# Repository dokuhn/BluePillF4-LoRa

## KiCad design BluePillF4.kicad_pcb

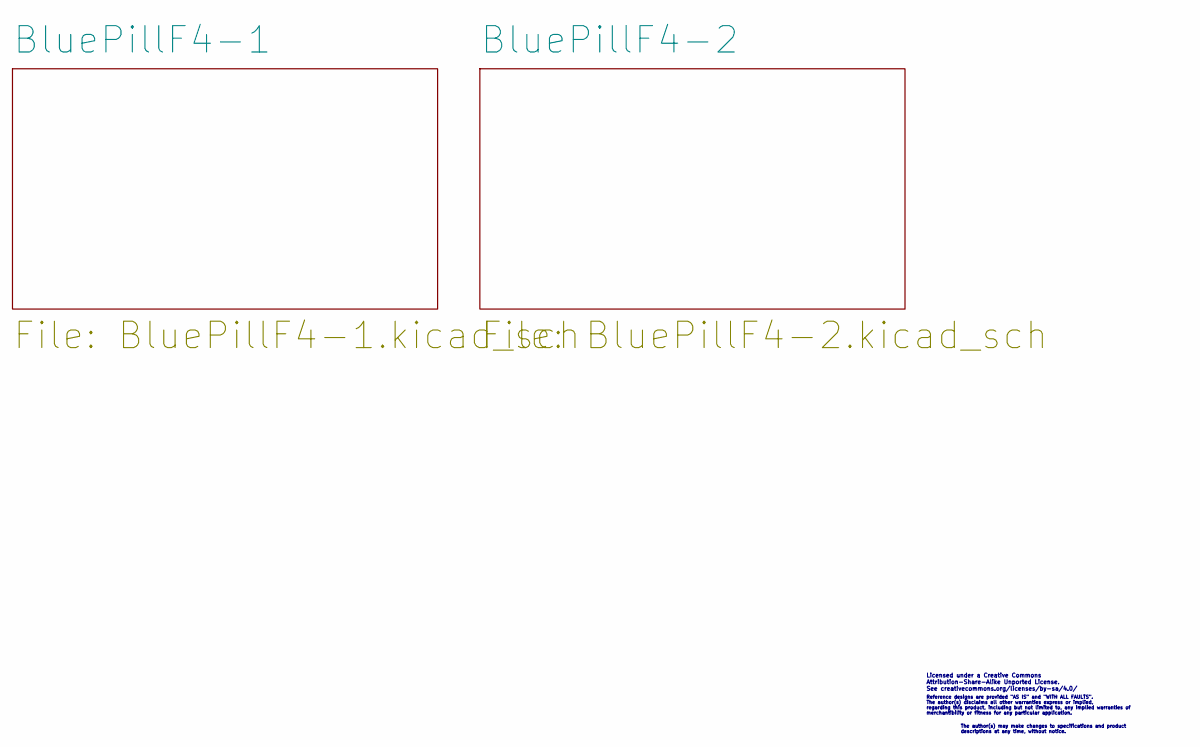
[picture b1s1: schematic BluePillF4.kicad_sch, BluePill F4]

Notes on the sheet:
Licensed under a Creative Commons Attribution-Share-Alike Unported License. See creativecommons.org/licenses/by-sa/4.0/
regarding this product, including but not limited to, any implied warranties of
merchantibility or fitness for any particular application.
Reference designs are provided "AS IS" and "WITH ALL FAULTS".
The author(s) disclaims all other warranties express or implied,
descriptions at any time, without notice.
The author(s) may make changes to specifications and product

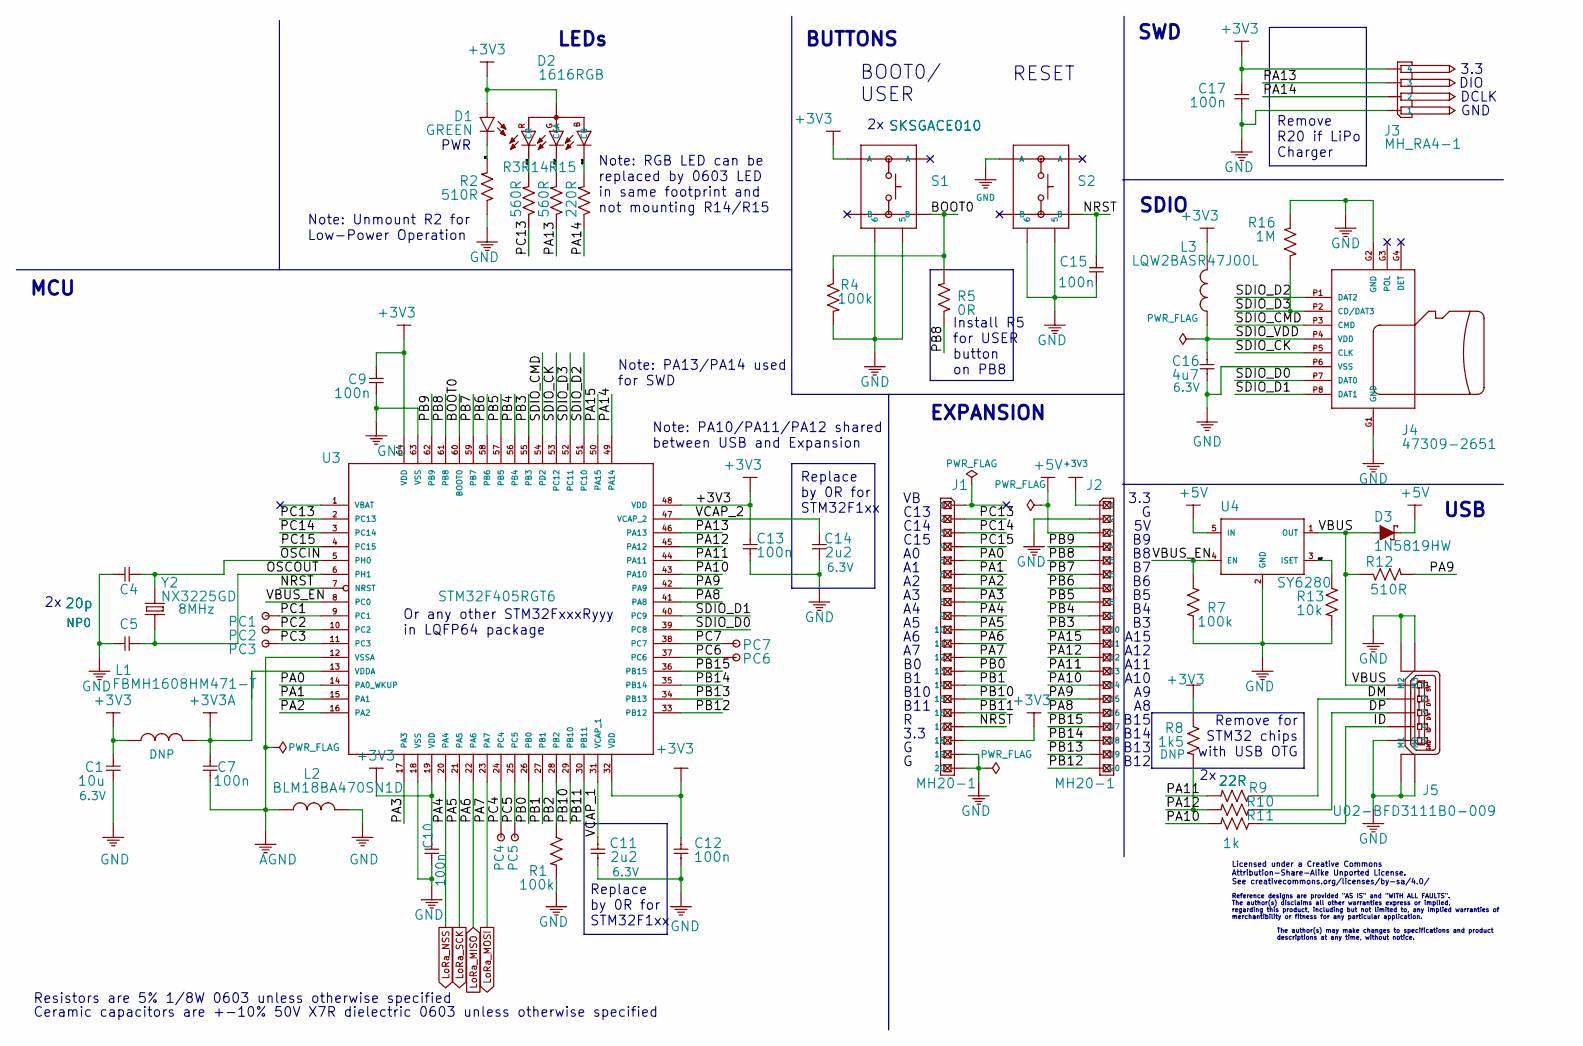
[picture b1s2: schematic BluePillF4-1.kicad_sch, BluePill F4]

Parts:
C1: 10u; C0603; PARTNO C0603_10u_X7R_10%_CER_6V3
C4, C5: 20p; C0603; PARTNO C0603_20p_NP0_5%_CER_50V
C7, C9, C10, C12, C13, C15, C17: 100n; C0603; PARTNO C0603_100n_X7R_10%_CER_50V
C11, C14: 2u2; C0603; PARTNO C0603_2u2_X7R_10%_CER_6V3
C16: 4u7; C0603; PARTNO C0603_4u7_X7R_10%_CER_6V3
D1: GREEN; LED0603; PARTNO LED0603-GREEN
D2: 1616RGB; PARTNO LED1616-RGB
D3: 1N5819HW; SOD-123; PARTNO 1N5819HW
J1, J2: MH20-1; MH20-1-0.1; PARTNO MH20-1-0.1
J3: MH_RA4-1; MH_RA4-1-0.1; PARTNO MH_RA4-1-0.1
J4: 47309-2651; PARTNO 47309-2651
J5: U02-BFD3111B0-009; PARTNO U02-BFD3111B0-009
L1: FBMH1608HM471-T; FB0603; PARTNO FBMH1608HM471-T
L2: BLM18BA470SN1D; FB0603; PARTNO BLM18BA470SN1D
L3: LQW2BASR47J00L; FB0805; PARTNO LQW2BASR47J00L
PC1, PC2, PC3, PC4, PC5, PC6, PC7: TEST_PAD
R1, R4, R7: 100k; R0603; PARTNO R0603_100k_5%_125mW
R2, R12: 510R; R0603; PARTNO R0603_510R_5%_125mW
R3, R14: 560R; R0603; PARTNO R0603_510R_5%_125mW
R5: 0R; R0603; PARTNO R0603_510R_5%_125mW
R8: 1k5; R0603; PARTNO R0603_1k5_5%_125mW
R9, R10: 22R; R0603; PARTNO R0603_22R_5%_125mW
R11: 1k; R0603; PARTNO R0603_1k_5%_125mW
R13: 10k; R0603; PARTNO R0603_10k_5%_125mW
R15: 220R; R0603; PARTNO R0603_510R_5%_125mW
R16: 1M; R0603; PARTNO R0603_1M_5%_125mW
S1, S2: SKSGACE010; PARTNO SKSGACE010
U3: STM32F405RGT6; LQFP64; PARTNO STM32F405RGT6
U4: SY6280; SOT23-5; PARTNO SY6280AAC
Y2: NX3225GD; CRYSTAL_32X25_2P; PARTNO NX3225GD-8MHZ-STD-CRA-3

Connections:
+3V3: C1.1, C9.2, C10.2, C12.1, C13.1, C17.2, D1.2 (A), D2.4 (A), J1.18, J2.1, J3.4, L1.1, L3.2, R8.1, S1.3 (A), U3.19 (VDD), U3.32 (VDD), U3.48 (VDD), U3.64 (VDD); also elsewhere on the board
+3V3A: C7.2, L1.2, U3.13 (VDDA)
+5V: D3.C, J2.3, U4.5 (IN); also elsewhere on the board
/BluePillF4-1/BOOT0: R4.1, R5.2, S1.2 (B), U3.60 (BOOT0)
/BluePillF4-1/D1: D1.1 (C), R2.2
/BluePillF4-1/D2_B: D2.3 (CB), R15.2
/BluePillF4-1/D2_G: D2.2 (CG), R14.2
/BluePillF4-1/D2_R: D2.1 (CR), R3.2
/BluePillF4-1/DM: J5.2, R9.1
/BluePillF4-1/DP: J5.3, R10.1
/BluePillF4-1/ID: J5.4, R11.1
/BluePillF4-1/ISET: R13.1, U4.3 (ISET)
/BluePillF4-1/NRST: C15.2, J1.17, S2.2 (B), U3.7 (NRST)
/BluePillF4-1/OSCIN: C4.1, U3.5 (PH0), Y2.2
/BluePillF4-1/OSCOUT: C5.1, U3.6 (PH1), Y2.1
/BluePillF4-1/PA0: J1.5, U3.14 (PA0_WKUP)
/BluePillF4-1/PA1: J1.6, U3.15 (PA1)
/BluePillF4-1/PA2: J1.7, U3.16 (PA2)
/BluePillF4-1/PA3: J1.8, U3.17 (PA3)
/BluePillF4-1/PA8: J2.16, U3.41 (PA8)
/BluePillF4-1/PA9: J2.15, R12.2, U3.42 (PA9)
/BluePillF4-1/PA10: J2.14, R11.2, U3.43 (PA10)
/BluePillF4-1/PA11: J2.13, R9.2, U3.44 (PA11)
/BluePillF4-1/PA12: J2.12, R8.2, R10.2, U3.45 (PA12)
/BluePillF4-1/PA13: J3.3, R14.1, U3.46 (PA13)
/BluePillF4-1/PA14: J3.2, R15.1, U3.49 (PA14)
/BluePillF4-1/PA15: J2.11, U3.50 (PA15)
/BluePillF4-1/PB0: J1.13, U3.26 (PB0)
/BluePillF4-1/PB1: J1.14, U3.27 (PB1)
/BluePillF4-1/PB2: R1.1, U3.28 (PB2)
/BluePillF4-1/PB3: J2.10, U3.55 (PB3)
/BluePillF4-1/PB4: J2.9, U3.56 (PB4)
/BluePillF4-1/PB5: J2.8, U3.57 (PB5)
/BluePillF4-1/PB6: J2.7, U3.58 (PB6)
/BluePillF4-1/PB7: J2.6, U3.59 (PB7)
/BluePillF4-1/PB8: J2.5, R5.1, U3.61 (PB8)
/BluePillF4-1/PB9: J2.4, U3.62 (PB9)
/BluePillF4-1/PB10: J1.15, U3.29 (PB10)
/BluePillF4-1/PB11: J1.16, U3.30 (PB11)
/BluePillF4-1/PB12: J2.20, U3.33 (PB12)
/BluePillF4-1/PB13: J2.19, U3.34 (PB13)
/BluePillF4-1/PB14: J2.18, U3.35 (PB14)
/BluePillF4-1/PB15: J2.17, U3.36 (PB15)
/BluePillF4-1/PC1: PC1.1 (PP), U3.9 (PC1)
/BluePillF4-1/PC2: PC2.1 (PP), U3.10 (PC2)
/BluePillF4-1/PC3: PC3.1 (PP), U3.11 (PC3)
/BluePillF4-1/PC4: PC4.1 (PP), U3.24 (PC4)
/BluePillF4-1/PC5: PC5.1 (PP), U3.25 (PC5)
/BluePillF4-1/PC6: PC6.1 (PP), U3.37 (PC6)
/BluePillF4-1/PC7: PC7.1 (PP), U3.38 (PC7)
/BluePillF4-1/PC13: J1.2, R3.1, U3.2 (PC13)
/BluePillF4-1/PC14: J1.3, U3.3 (PC14)
/BluePillF4-1/PC15: J1.4, U3.4 (PC15)
/BluePillF4-1/SDIO_CK: J4.P5 (CLK), U3.53 (PC12)
/BluePillF4-1/SDIO_CMD: J4.P3 (CMD), U3.54 (PD2)
/BluePillF4-1/SDIO_D0: J4.P7 (DAT0), U3.39 (PC8)
/BluePillF4-1/SDIO_D1: J4.P8 (DAT1), U3.40 (PC9)
/BluePillF4-1/SDIO_D2: J4.P1 (DAT2), U3.51 (PC10)
/BluePillF4-1/SDIO_D3: J4.P2 (CD/DAT3), R16.1, U3.52 (PC11)
/BluePillF4-1/SDIO_VDD: C16.2, J4.P4 (VDD), L3.1
/BluePillF4-1/VBUS: D3.A, J5.1, R12.1, U4.1 (OUT)
/BluePillF4-1/VBUS_EN: R7.1, U3.8 (PC0), U4.4 (EN)
/BluePillF4-1/VCAP_1: C11.2, U3.31 (VCAP_1)
/BluePillF4-1/VCAP_2: C14.2, U3.47 (VCAP_2)
AGND: C7.1, L2.1, U3.12 (VSSA)
GND: C1.2, C4.2, C5.2, C9.1, C10.1, C11.1, C12.2, C13.2, C14.1, C15.1, C16.1, C17.1, J1.19, J1.20, J2.2, J3.1, J4.G1 (GND), J4.G2 (GND), J4.P6 (VSS), J5.5, J5.S$1 (M0), J5.S$2 (M1), J5.S$3 (M2), J5.S$4 (M3), L2.2, R1.2, R2.1, R4.2, R7.2, R13.2, R16.2, S1.5, S1.6, S2.3 (A), S2.5, S2.6, U3.18 (VSS), U3.63 (VSS), U4.2 (GND); also elsewhere on the board
LoRa_MISO: J1.11, U3.22 (PA6); also elsewhere on the board
LoRa_MOSI: J1.12, U3.23 (PA7); also elsewhere on the board
LoRa_NSS: J1.9, U3.20 (PA4); also elsewhere on the board
LoRa_SCK: J1.10, U3.21 (PA5); also elsewhere on the board

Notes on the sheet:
3.3
A11
B14
BOOT0/ USER
C13
SWD
C15
RESET
LEDs
B13
Licensed under a Creative Commons Attribution-Share-Alike Unported License. See creativecommons.org/licenses/by-sa/4.0/
C14
USB
Note: Unmount R2 for Low-Power Operation
EXPANSION
Resistors are 5% 1/8W 0603 unless otherwise specified
MCU
Replace by 0R for STM32F1xx
GND
merchantibility or fitness for any particular application.
The author(s) may make changes to specifications and product
SDIO
B15
descriptions at any time, without notice.
A10
Remove R20 if LiPo Charger
Reference designs are provided "AS IS" and "WITH ALL FAULTS".
Or any other STM32FxxxRyyy in LQFP64 package
Ceramic capacitors are +-10% 50V X7R dielectric 0603 unless otherwise specified
A15
B12
B11
The author(s) disclaims all other warranties express or implied,
Install R5 for USER button on PB8
DCLK
A12
Remove for STM32 chips with USB OTG
Note: RGB LED can be replaced by 0603 LED in same footprint and not mounting R14/R15
PWR
B10

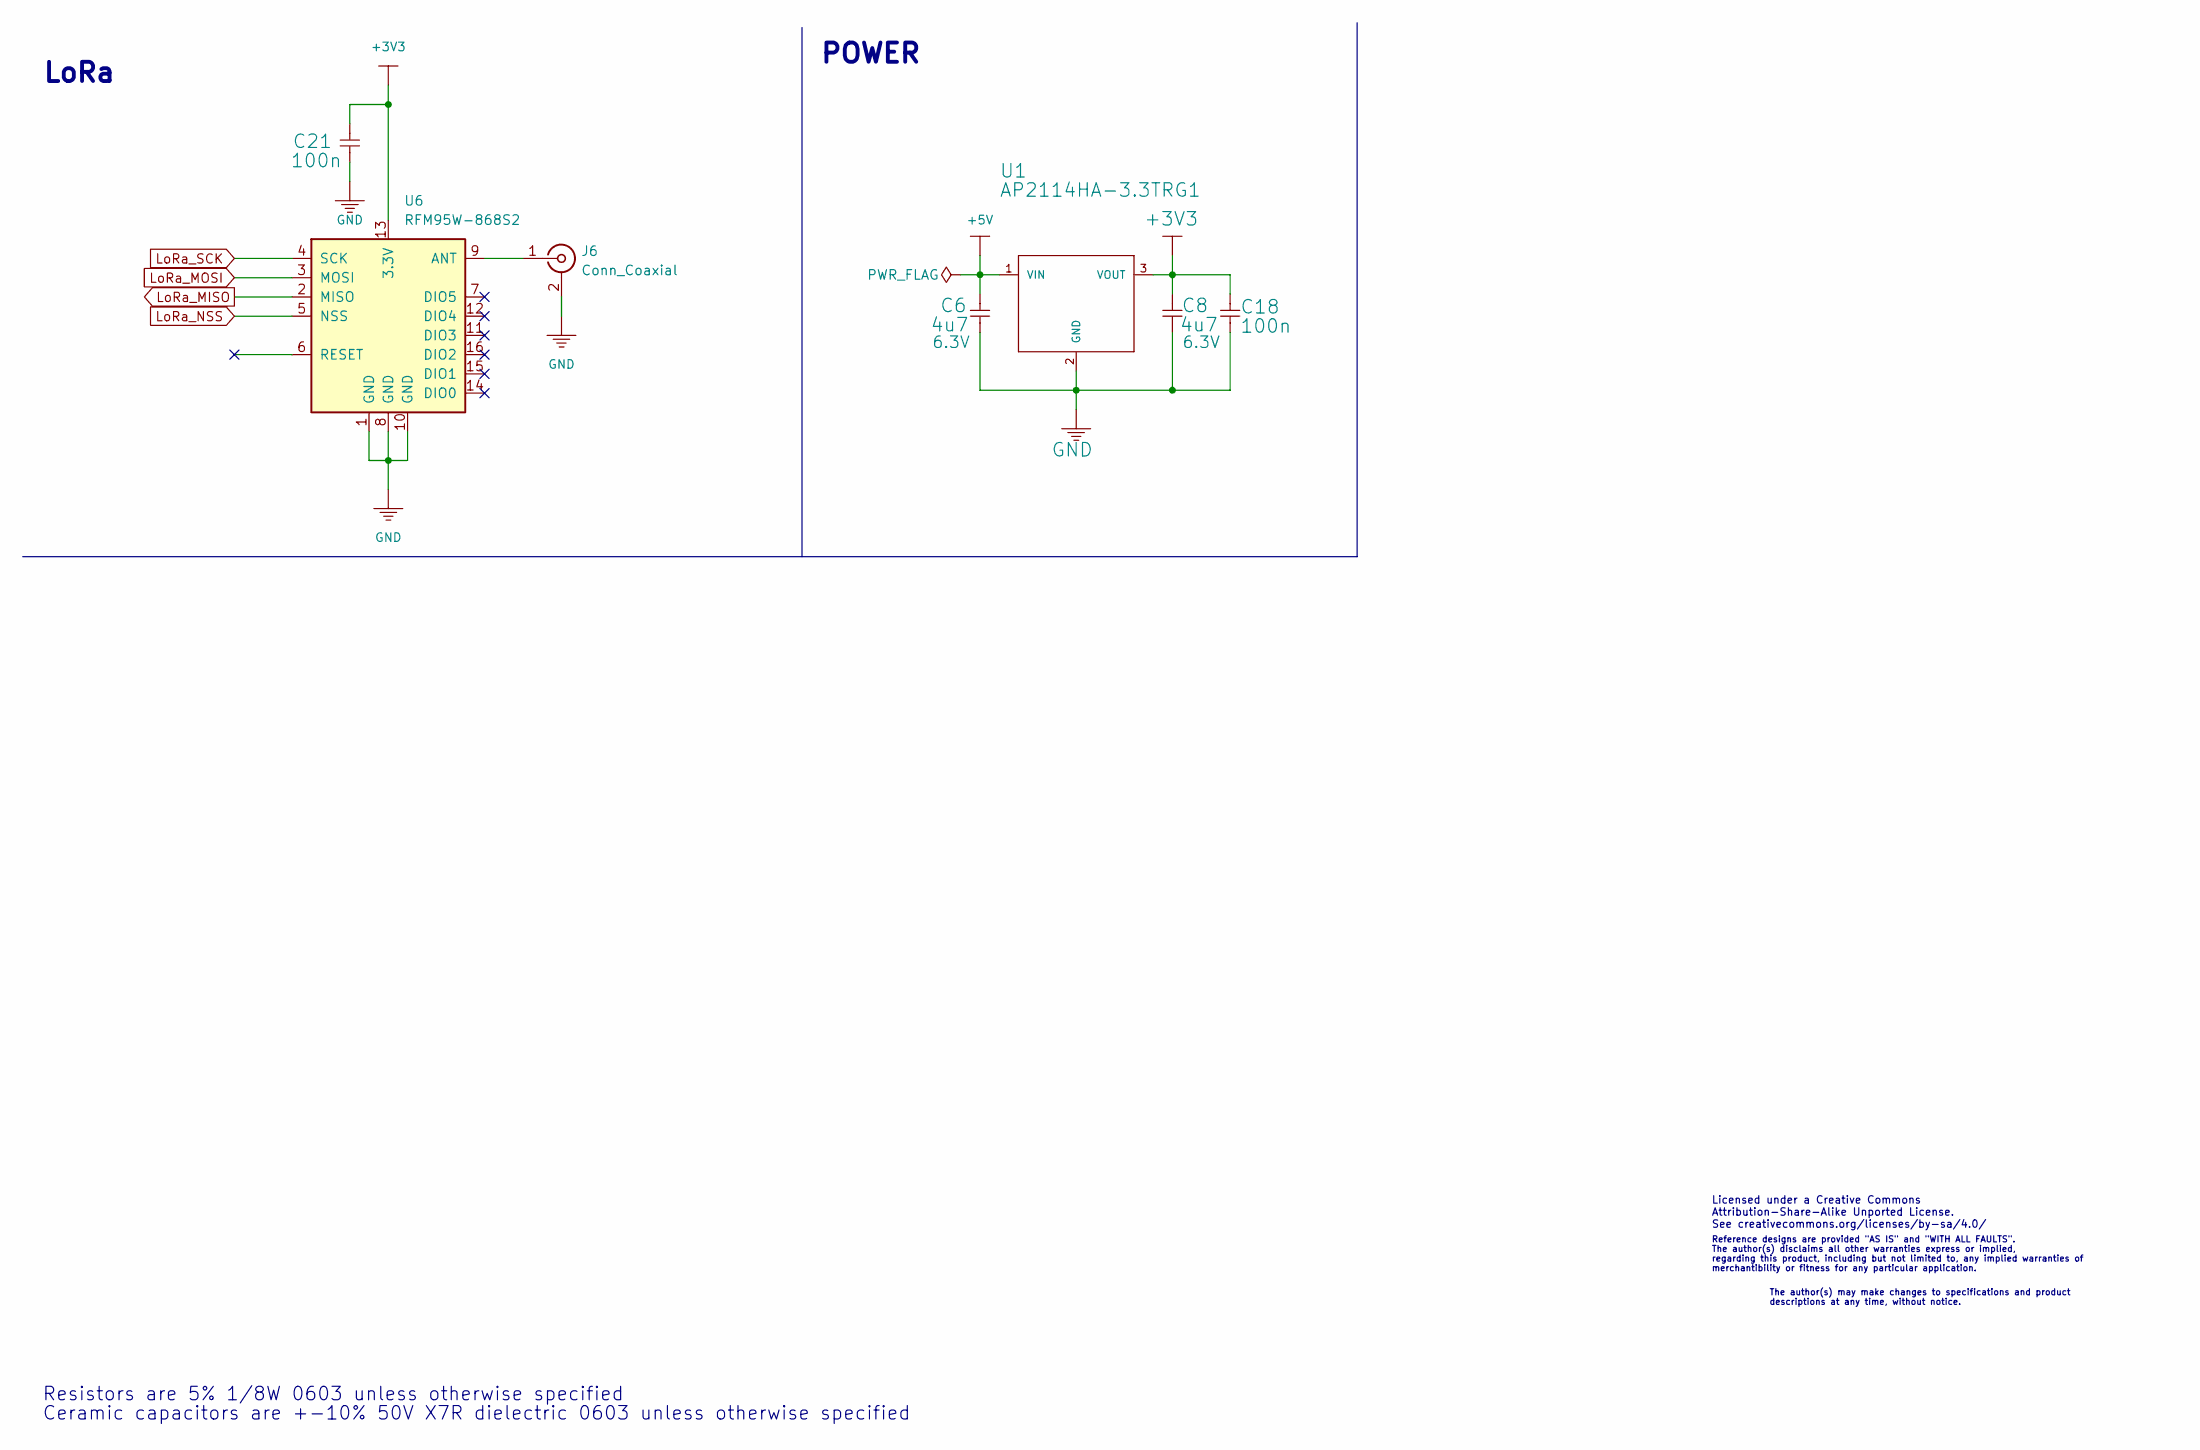
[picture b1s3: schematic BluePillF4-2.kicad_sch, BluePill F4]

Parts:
C6, C8: 4u7; C0603; PARTNO C0603_4u7_X7R_10%_CER_6V3
C18, C21: 100n; C0603; PARTNO C0603_100n_X7R_10%_CER_50V
J6: Conn_Coaxial; SMA_Molex_73251-1153_EdgeMount_Horizontal
U1: AP2114HA-3.3TRG1; SOT223; PARTNO AP2114HA3.3-TRG1
U6: RFM95W-868S2; HOPERF_RFM9XW_SMD

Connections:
+3V3: C8.1, C18.2, C21.2, U1.3 (VOUT), U6.13 (3.3V); also elsewhere on the board
+5V: C6.1, U1.1 (VIN); also elsewhere on the board
GND: C6.2, C8.2, C18.1, C21.1, J6.2 (Ext), U1.2 (GND), U1.PAD (GND), U6.1 (GND), U6.8 (GND), U6.10 (GND); also elsewhere on the board
LoRa_MISO: U6.2 (MISO); also elsewhere on the board
LoRa_MOSI: U6.3 (MOSI); also elsewhere on the board
LoRa_NSS: U6.5 (NSS); also elsewhere on the board
LoRa_SCK: U6.4 (SCK); also elsewhere on the board
unnamed: J6.1 (In), U6.9 (ANT)

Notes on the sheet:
The author(s) disclaims all other warranties express or implied,
The author(s) may make changes to specifications and product
POWER
Ceramic capacitors are +-10% 50V X7R dielectric 0603 unless otherwise specified
regarding this product, including but not limited to, any implied warranties of
descriptions at any time, without notice.
Reference designs are provided "AS IS" and "WITH ALL FAULTS".
merchantibility or fitness for any particular application.
LoRa
Resistors are 5% 1/8W 0603 unless otherwise specified
Licensed under a Creative Commons Attribution-Share-Alike Unported License. See creativecommons.org/licenses/by-sa/4.0/

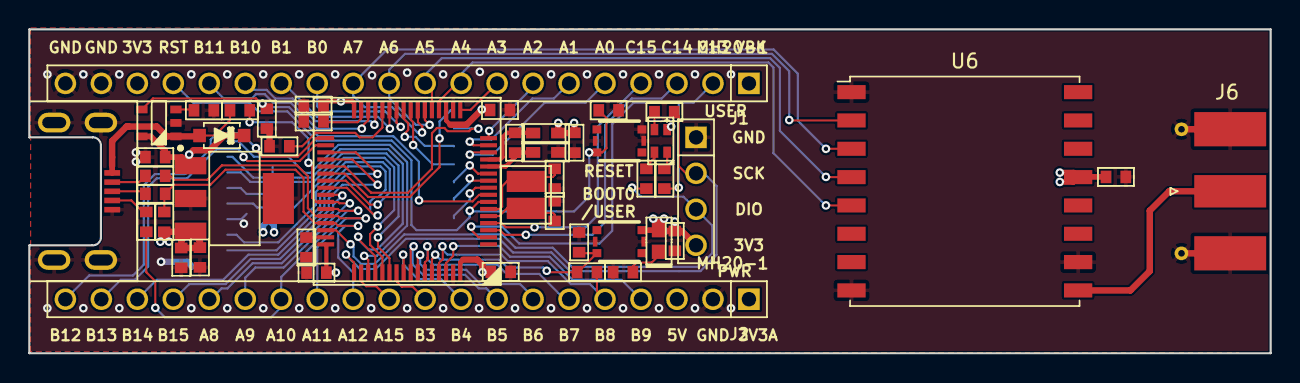
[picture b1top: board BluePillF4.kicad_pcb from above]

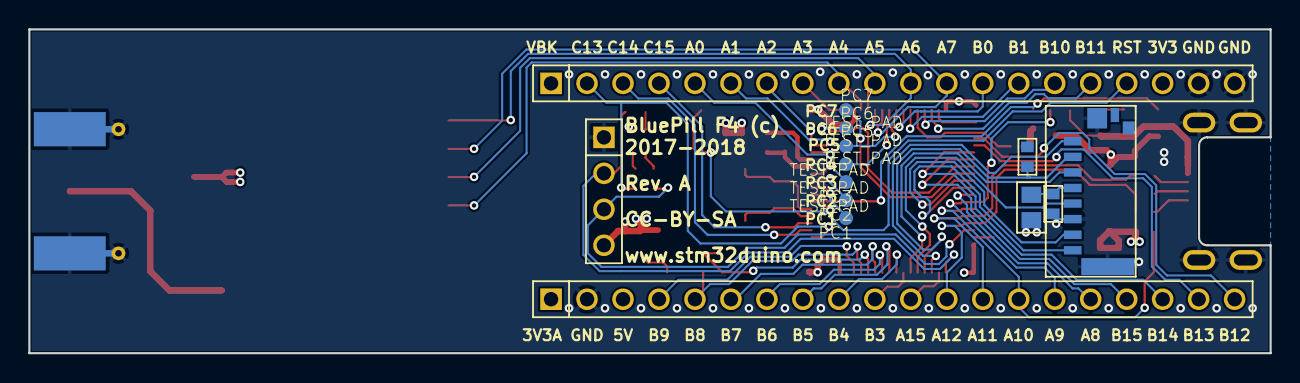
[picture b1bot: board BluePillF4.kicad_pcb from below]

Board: 4 copper layers, 87.6 x 22.9 mm, 58 parts (11 on the bottom side), 71 nets.

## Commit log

2022-04-10 first init
2022-04-17 adding 3D shape for Molex 73251-1153 SMA Connector
2022-04-18 Removed unnecessary components like LiPo charger and fixed most errors. First connections between LoRa module and MCU created in the schematic.
2022-04-24 Moving some PWR-Nets like 5V to the Bot Layer.
2022-04-24 Added GND at inner level and routed some traces nicely.
2022-04-24 Updating 3D Model file
2022-04-27 some traces nicely arranged. 3V3 still needs to be made nice (no side connection to MCU)

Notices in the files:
BluePillF4-1.kicad_sch:
© 2017-2018 www.stm32duino.com, All rights reserved.
BluePillF4.kicad_pcb:
© 2017-2018, All rights reserved.
CC-BY-SA
